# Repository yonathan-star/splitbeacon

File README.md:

# SplitBeacon

**Half Life Week 4: Displays — Tier 3 design target.** SplitBeacon is Yonathan’s project. Codex assisted with review and submission preparation. The owner confirmed the existing five design sections and their 20-hour total on November 1, 2026. Individual session dates were not supplied; records are retrospective. No physical build or bench testing is represented as completed.

SplitBeacon is a standalone training and repetition timer that turns lap pacing into a visible pattern. Two RGB panels form a 16-by-4 progress display while a small TFT shows precise elapsed time, target time, recent splits, and a session summary. It is useful at a desk, in a practice space, or during dry-land training where unlocking a phone interrupts the session.

## What makes it original

The project combines an adjustable target with a target value latched at the start of each lap. Turning the knob during a lap changes the next target without rewriting the current comparison. The RGB history view encodes whether completed laps were early, close to target, or late. A separate TFT preserves readable numbers while the RGB panels remain glanceable. The design includes a custom controller PCB, analog light sensing, protected external power, a physical interface, original firmware, and a serviceable printable enclosure.

## Controls

- RUN pauses or resumes without counting paused wall time.
- LAP records the current split and starts the next lap. Splits shorter than 250ms are rejected.
- VIEW cycles timer, recent splits, and summary. Hold VIEW for two seconds to clear the session.
- TARGET selects 5–600 seconds. Changes apply to the next lap.
- BRIGHT changes the brightness ceiling; the light sensor reduces output in dark rooms.

The timer gives a short piezo cue when the target is reached. It stores up to 64 split records and saves history when paused. Restarting restores history, not an interrupted live stopwatch.

## Engineering files

- [Editable KiCad project](hardware/controller/controller.kicad_pro), [schematic](hardware/controller/controller.kicad_sch), [routed PCB](hardware/controller/controller.kicad_pcb), and [schematic plot](preview/controller.svg). Local footprints are bundled.
- [Fabrication Gerbers and drill ZIP](hardware/SplitBeacon-gerbers.zip). Board: 100x100mm, two layers, 1.6mm FR4, 1oz copper.
- [MicroPython firmware](firmware/main.py), portable [timer core](firmware/core.py), and original [ST7789 driver](firmware/st7789.py).
- [Parametric enclosure](mechanical/enclosure.scad) and six STL parts, including a tolerance coupon.
- [Full BOM](BOM.md), [purchase spreadsheet](outputs/splitbeacon/SplitBeacon-BOM.xlsx), and [CSV](BOM.csv).
- [Wiring](docs/WIRING.md), [assembly and flashing](docs/ASSEMBLY.md), [verification](docs/VERIFICATION.md), [journal](journal/JOURNAL.md), and [submission text](docs/SUBMISSION.md).

## Validation

Ten portable firmware tests pass. The routed PCB reports zero DRC violations, zero unconnected pads, and zero footprint errors. A separate check compares 88 connected logical pins between the schematic netlist and routed PCB. These checks do not replace bench testing or electrical ERC.

The RGB channels are capped at 16/255 in firmware. The external 5V input powers the displays through a 500mA PTC; a Schottky diode feeds Pico VSYS while keeping its USB supply isolated. Each FeatherWing already has a logic-level shifter, so each is driven through its default control pin on an independent Pico GPIO.

## Budget and scope

Purchased parts and a complete spool total $103.80 before PCB fabrication and final shipping/tax. The BOM exposes package quantities, shipping estimates and the funding gap. Actual supplier-cart screenshots are included. The original package records no purchases. Live submission status must be verified separately.

The scope targets Tier 3 through complete hardware, software and mechanical design. The program determines actual tier and eligibility. Media prepared for this submission uses the actual project files. Concept visualizations, CAD renders and any software simulations are labeled; they do not demonstrate a physical build. Personal work and time requirements must be supported by actual records. Existing AI-assistance credits are retained.

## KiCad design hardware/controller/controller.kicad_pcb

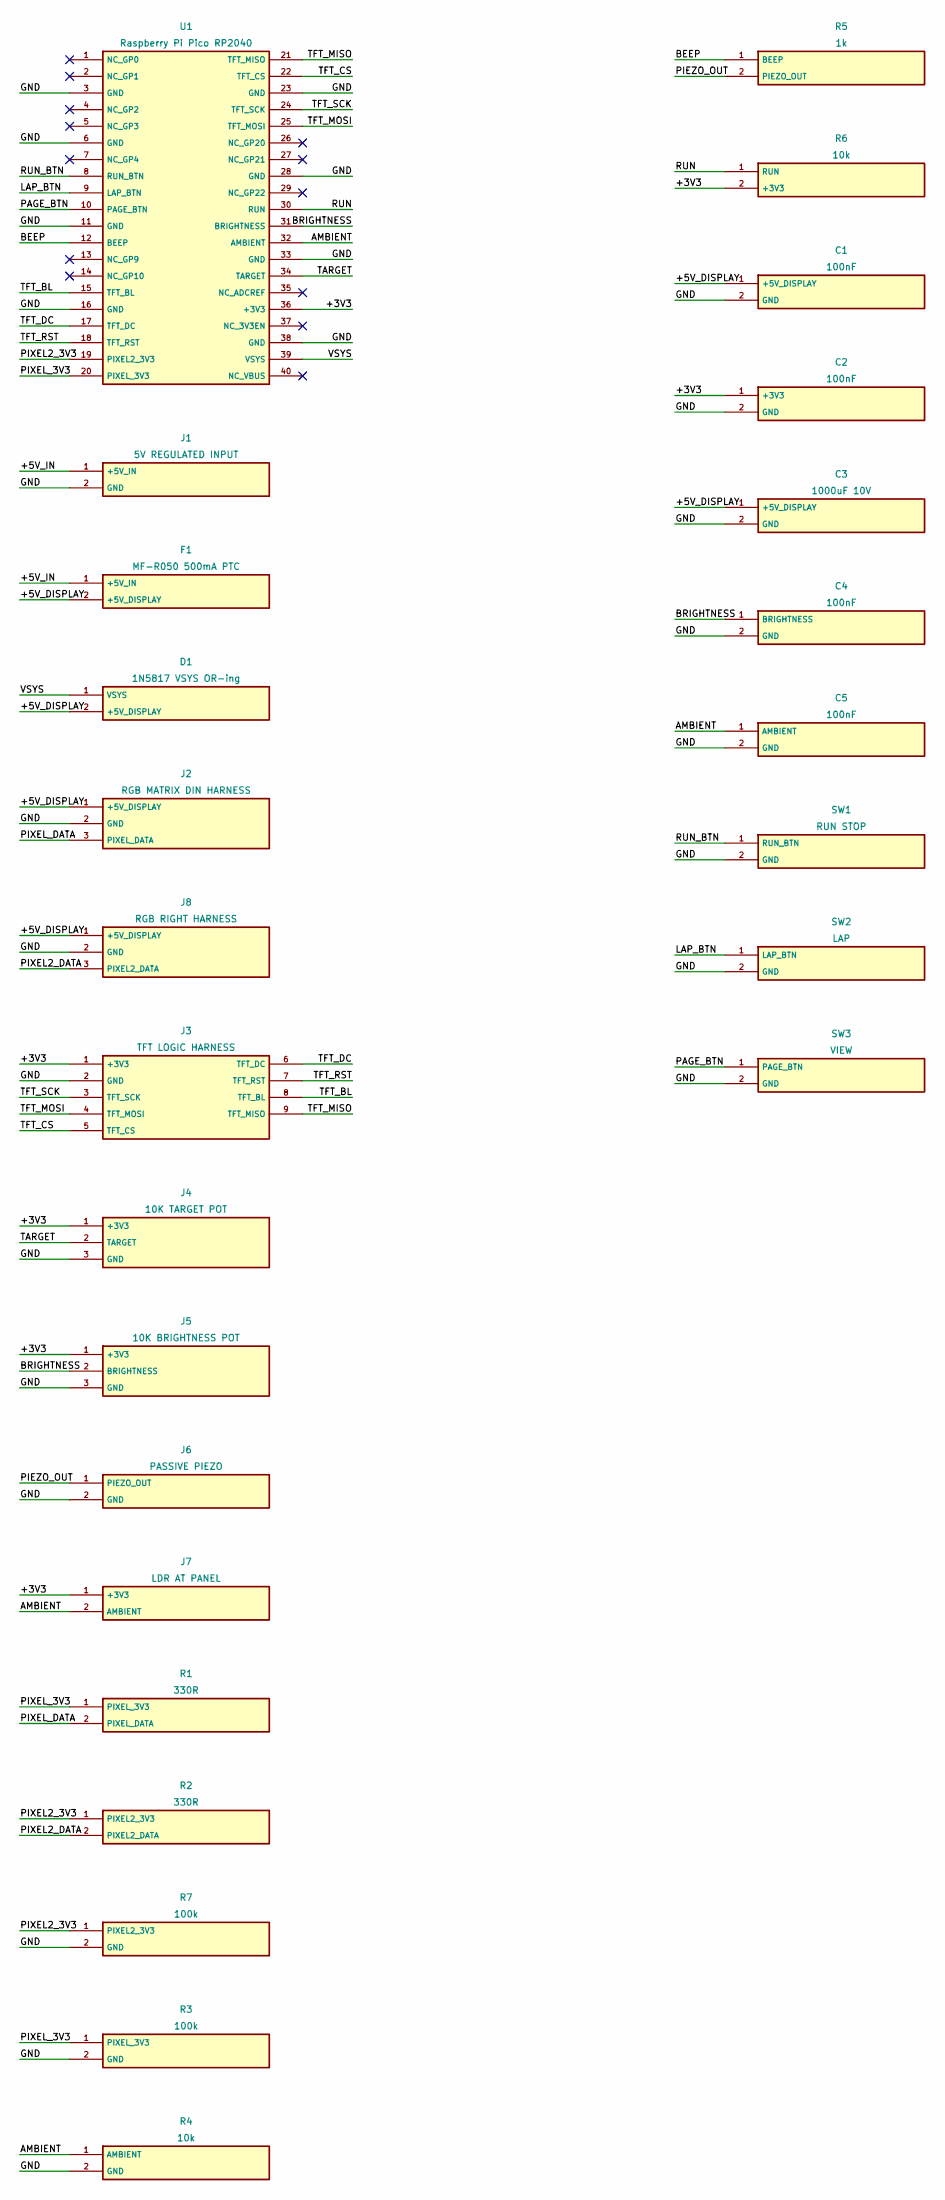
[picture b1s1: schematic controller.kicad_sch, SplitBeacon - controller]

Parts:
C1, C2, C4, C5: 100nF; C_Disc_D3.0mm_W1.6mm_P2.50mm
C3: 1000uF 10V; CP_Radial_D10.0mm_P5.00mm
D1: 1N5817 VSYS OR-ing; D_DO-41_SOD81_P10.16mm_Horizontal
F1: MF-R050 500mA PTC; PTC_5mm
J1: 5V REGULATED INPUT; PinHeader_1x02_P2.54mm_Vertical
J2: RGB MATRIX DIN HARNESS; PinHeader_1x03_P2.54mm_Vertical
J3: TFT LOGIC HARNESS; PinHeader_1x09_P2.54mm_Vertical
J4: 10K TARGET POT; PinHeader_1x03_P2.54mm_Vertical
J5: 10K BRIGHTNESS POT; PinHeader_1x03_P2.54mm_Vertical
J6: PASSIVE PIEZO; PinHeader_1x02_P2.54mm_Vertical
J7: LDR AT PANEL; PinHeader_1x02_P2.54mm_Vertical
J8: RGB RIGHT HARNESS; PinHeader_1x03_P2.54mm_Vertical
R1, R2: 330R; R_Axial_DIN0207_L6.3mm_D2.5mm_P10.16mm_Horizontal
R3, R7: 100k; R_Axial_DIN0207_L6.3mm_D2.5mm_P10.16mm_Horizontal
R4, R6: 10k; R_Axial_DIN0207_L6.3mm_D2.5mm_P10.16mm_Horizontal
R5: 1k; R_Axial_DIN0207_L6.3mm_D2.5mm_P10.16mm_Horizontal
SW1: RUN STOP; Button_6mm
SW2: LAP; Button_6mm
SW3: VIEW; Button_6mm
U1: Raspberry Pi Pico RP2040; Pico_Socket

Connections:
+3V3: C2.1 (+3V3), J3.1 (+3V3), J4.1 (+3V3), J5.1 (+3V3), J7.1 (+3V3), R6.2 (+3V3), U1.36 (+3V3)
+5V_DISPLAY: C1.1 (+5V_DISPLAY), C3.1 (+5V_DISPLAY), D1.2 (+5V_DISPLAY), F1.2 (+5V_DISPLAY), J2.1 (+5V_DISPLAY), J8.1 (+5V_DISPLAY)
+5V_IN: F1.1 (+5V_IN), J1.1 (+5V_IN)
AMBIENT: C5.1 (AMBIENT), J7.2 (AMBIENT), R4.1 (AMBIENT), U1.32 (AMBIENT)
BEEP: R5.1 (BEEP), U1.12 (BEEP)
BRIGHTNESS: C4.1 (BRIGHTNESS), J5.2 (BRIGHTNESS), U1.31 (BRIGHTNESS)
GND: C1.2 (GND), C2.2 (GND), C3.2 (GND), C4.2 (GND), C5.2 (GND), J1.2 (GND), J2.2 (GND), J3.2 (GND), J4.3 (GND), J5.3 (GND), J6.2 (GND), J8.2 (GND), R3.2 (GND), R4.2 (GND), R7.2 (GND), SW1.2 (GND), SW2.2 (GND), SW3.2 (GND), U1.3 (GND), U1.6 (GND), U1.11 (GND), U1.16 (GND), U1.23 (GND), U1.28 (GND), U1.33 (GND), U1.38 (GND)
LAP_BTN: SW2.1 (LAP_BTN), U1.9 (LAP_BTN)
PAGE_BTN: SW3.1 (PAGE_BTN), U1.10 (PAGE_BTN)
PIEZO_OUT: J6.1 (PIEZO_OUT), R5.2 (PIEZO_OUT)
PIXEL2_3V3: R2.1 (PIXEL2_3V3), R7.1 (PIXEL2_3V3), U1.19 (PIXEL2_3V3)
PIXEL2_DATA: J8.3 (PIXEL2_DATA), R2.2 (PIXEL2_DATA)
PIXEL_3V3: R1.1 (PIXEL_3V3), R3.1 (PIXEL_3V3), U1.20 (PIXEL_3V3)
PIXEL_DATA: J2.3 (PIXEL_DATA), R1.2 (PIXEL_DATA)
RUN: R6.1 (RUN), U1.30 (RUN)
RUN_BTN: SW1.1 (RUN_BTN), U1.8 (RUN_BTN)
TARGET: J4.2 (TARGET), U1.34 (TARGET)
TFT_BL: J3.8 (TFT_BL), U1.15 (TFT_BL)
TFT_CS: J3.5 (TFT_CS), U1.22 (TFT_CS)
TFT_DC: J3.6 (TFT_DC), U1.17 (TFT_DC)
TFT_MISO: J3.9 (TFT_MISO), U1.21 (TFT_MISO)
TFT_MOSI: J3.4 (TFT_MOSI), U1.25 (TFT_MOSI)
TFT_RST: J3.7 (TFT_RST), U1.18 (TFT_RST)
TFT_SCK: J3.3 (TFT_SCK), U1.24 (TFT_SCK)
VSYS: D1.1 (VSYS), U1.39 (VSYS)

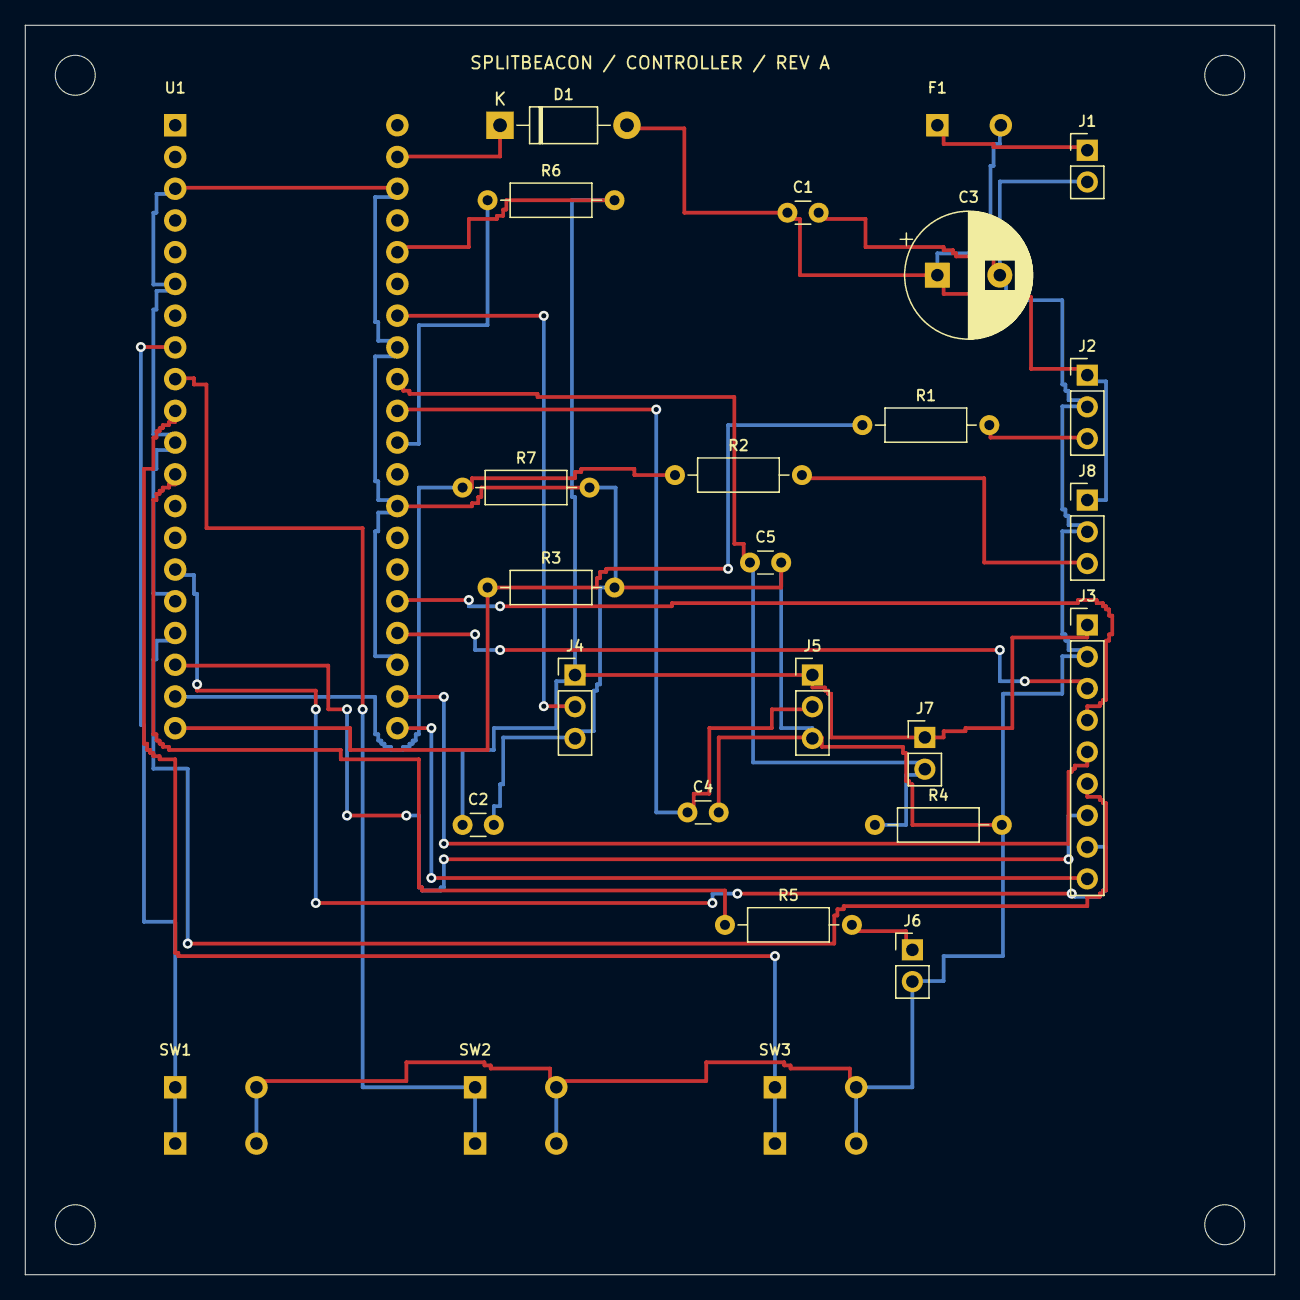
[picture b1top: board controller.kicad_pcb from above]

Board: 2 copper layers, 100.0 x 100.0 mm, 30 parts (0 on the bottom side), 25 nets.

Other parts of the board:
H44, H496, H964, H9696: MountingHole_3.2mm_M3

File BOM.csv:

References,Item,Vendor,SKU,Purchase quantity,Unit price USD,Quantity used,Source,Notes
DISP1 DISP2,NeoPixel FeatherWing 4x8 RGB,Adafruit,2945,2,14.95,2,https://www.adafruit.com/product/2945,Two independent GPIO data inputs; built-in level shifters
DISP3,1.14 inch ST7789 TFT 240x135,Adafruit,4383,1,9.95,1,https://www.adafruit.com/product/4383,
U1,Pico RP2040 with loose headers,Adafruit,4883,1,5,1,https://www.adafruit.com/product/4883,Solder directly; supplied 2x20 headers
RV1 RV2,10k linear panel potentiometer,Adafruit,562,2,0.95,2,https://www.adafruit.com/product/562,
SW1 SW2 SW3,6mm tactile button 20 pack,Adafruit,367,1,2.5,3,https://www.adafruit.com/product/367,17 spare buttons
C1 C2 C4 C5,100nF ceramic capacitor 10 pack,Adafruit,753,1,1.95,4,https://www.adafruit.com/product/753,Six spare capacitors; 2.54mm leads
PSU,5V 4A regulated power supply,Adafruit,1466,1,14.95,1,https://www.adafruit.com/product/1466,2.1mm centre positive; external low-voltage input
DC1,2.1mm female jack to screw terminal,Adafruit,368,1,2,1,https://www.adafruit.com/product/368,
BZ1,PS1240 passive piezo,Adafruit,160,1,1.5,1,https://www.adafruit.com/product/160,
LDR1,CdS photocell,Adafruit,161,1,0.95,1,https://www.adafruit.com/product/161,
HARNESS,40 female/female 150mm jumper wires,Adafruit,266,1,3.95,27,https://www.adafruit.com/product/266,Trim and solder bare sensor/pot ends; retain female board ends
F1,MF-R050 500mA radial PTC,DigiKey,MF-R050-ND,1,0.47,1,https://www.digikey.com/en/products/detail/bourns-inc/MF-R05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,5.1mm pitch
C3,EEU-FR1A102 1000uF 10V,DigiKey,P124221-ND,1,1.15,1,https://www.digikey.com/en/products/detail/panasonic-industr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,10mm body; 5mm pitch; 17.5mm max height
R1 R2,330 ohm axial 1/4W 5%,DigiKey,CF14JT330RCT-ND,2,0.1,2,https://www.digikey.com/en/products/detail/stackpole-electro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,Cart has separate R1 and R2 lines
R3 R7,100k axial 1/4W 5%,DigiKey,CF14JT100KCT-ND,2,0.1,2,https://www.digikey.com/en/products?keywords=CF14JT100K,Cart has separate R3 and R7 lines
R4 R6,10k axial 1/4W 5%,DigiKey,CF14JT10K0CT-ND,2,0.1,2,https://www.digikey.com/en/products?keywords=CF14JT10K0,
R5,1k axial 1/4W 5%,DigiKey,CF14JT1K00CT-ND,1,0.1,1,https://www.digikey.com/en/products?keywords=CF14JT1K00,
D1,1N5817-T Schottky diode DO41,DigiKey,1N5817DICT-ND,1,0.37,1,https://www.digikey.com/en/products/detail/diodes-incorporat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,
CASE,M3x6 Phillips pan-head screw,DigiKey,335-1156-ND,16,0.473,16,https://www.digikey.com/en/products/detail/apm-hexseal/RM3X6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,4 PCB + 4 lid + 8 display retainers; cart rounds line to $7.57
PRINT,Black PLA 1.75mm 1kg spool,Polymaker,CA19006,1,18.99,1,https://shop.polymaker.com/products/panchroma-pla?variant=44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,Full spool purchase; print consumes only a portion

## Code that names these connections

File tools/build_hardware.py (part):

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comp('controller','J1','5V REGULATED INPUT',{1:'+5V_IN',2:'GND'},'Connector_PinHeader_2.54mm:PinHeader_1x02_P2.54mm_Vertical',85,10)
comp('controller','F1','MF-R050 500mA PTC',{1:'+5V_IN',2:'+5V_DISPLAY'},'SplitBeacon:PTC_5mm',73,8)
comp('controller','D1','1N5817 VSYS OR-ing',{1:'VSYS',2:'+5V_DISPLAY'},'Diode_THT:D_DO-41_SOD81_P10.16mm_Horizontal',38,8)
comp('controller','J2','RGB MATRIX DIN HARNESS',{1:'+5V_DISPLAY',2:'GND',3:'PIXEL_DATA'},'Connector_PinHeader_2.54mm:PinHeader_1x03_P2.54mm_Vertical',85,28)
comp('controller','J8','RGB RIGHT HARNESS',{1:'+5V_DISPLAY',2:'GND',3:'PIXEL2_DATA'},'Connector_PinHeader_2.54mm:PinHeader_1x03_P2.54mm_Vertical',85,38)
comp('controller','J3','TFT LOGIC HARNESS',{1:'+3V3',2:'GND',3:'TFT_SCK',4:'TFT_MOSI',5:'TFT_CS',6:'TFT_DC',7:'TFT_RST',8:'TFT_BL',9:'TFT_MISO'},'Connector_PinHeader_2.54mm:PinHeader_1x09_P2.54mm_Vertical',85,48)
comp('controller','J4','10K TARGET POT',{1:'+3V3',2:'TARGET',3:'GND'},'Connector_PinHeader_2.54mm:PinHeader_1x03_P2.54mm_Vertical',44,52)
comp('controller','J5','10K BRIGHTNESS POT',{1:'+3V3',2:'BRIGHTNESS',3:'GND'},'Connector_PinHeader_2.54mm:PinHeader_1x03_P2.54mm_Vertical',63,52)
comp('controller','J6','PASSIVE PIEZO',{1:'PIEZO_OUT',2:'GND'},'Connector_PinHeader_2.54mm:PinHeader_1x02_P2.54mm_Vertical',71,74)
comp('controller','J7','LDR AT PANEL',{1:'+3V3',2:'AMBIENT'},'Connector_PinHeader_2.54mm:PinHeader_1x02_P2.54mm_Vertical',72,57)
comp('controller','R1','330R',{1:'PIXEL_3V3',2:'PIXEL_DATA'},'Resistor_THT:R_Axial_DIN0207_L6.3mm_D2.5mm_P10.16mm_Horizontal',67,32)
comp('controller','R2','330R',{1:'PIXEL2_3V3',2:'PIXEL2_DATA'},'Resistor_THT:R_Axial_DIN0207_L6.3mm_D2.5mm_P10.16mm_Horizontal',52,36)
comp('controller','R7','100k',{1:'PIXEL2_3V3',2:'GND'},'Resistor_THT:R_Axial_DIN0207_L6.3mm_D2.5mm_P10.16mm_Horizontal',35,37)
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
